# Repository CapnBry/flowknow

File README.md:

flowknow
========

ATmega-based flow meter and tally

Project directory structure
```
arduino/ - FlowKnow source code
eagle/   - Schematic and board design
```

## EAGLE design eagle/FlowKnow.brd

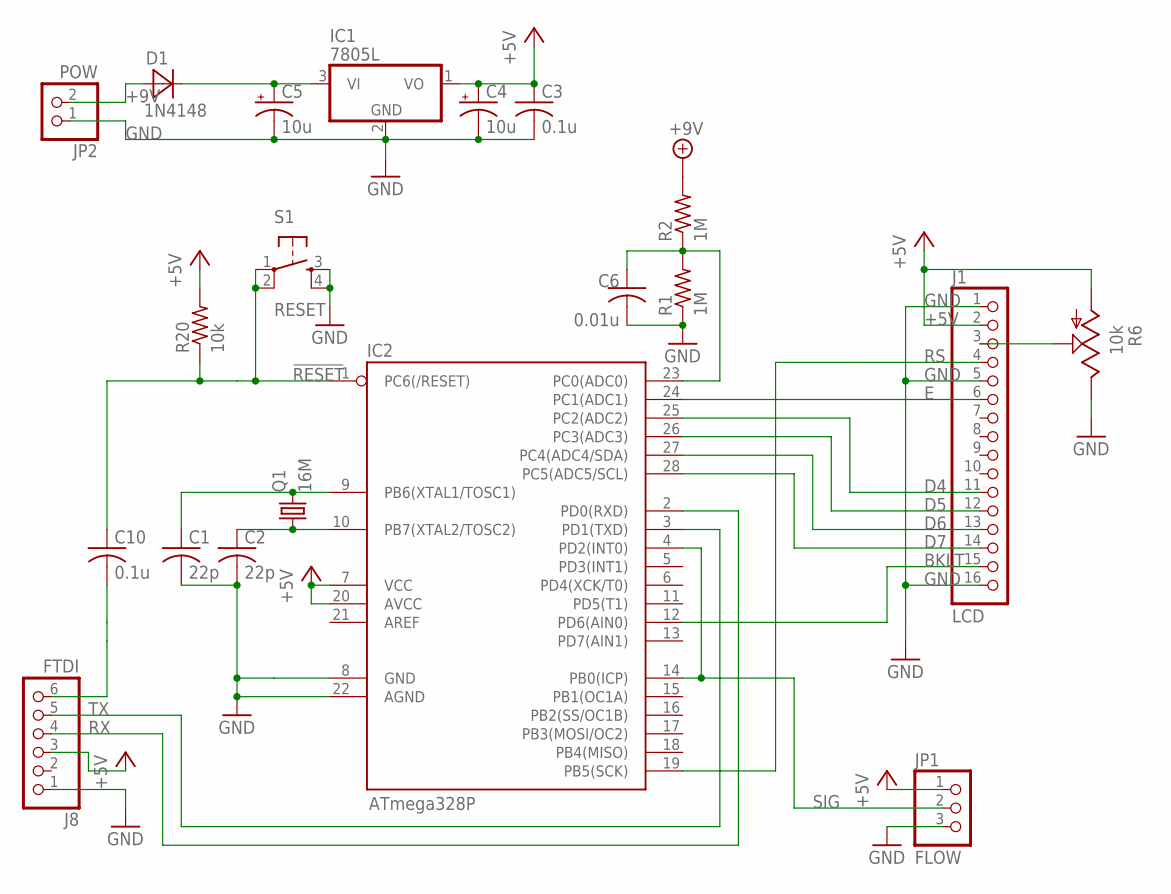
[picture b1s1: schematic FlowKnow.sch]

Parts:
C1, C2: 22p; C025-025X050
C3, C10: 0.1u; C025-025X050
C4: 10u; E2-4
C5: 10u; E2,5-5
C6: 0.01u; C025-025X050
D1: 1N4148; DO35-5
IC1: 7805L; TO92
IC2: ATmega328P; DIL28-3
J1: LCD; 1X16
J8: FTDI; 1X06/90
JP1: FLOW; 1X03/90
JP2: POW; 1X02
Q1: 16M; HC49/S
R1, R2: 1M; 0204/7
R6: 10k; CT6
R20: 10k; 0204/7
S1: RESET; TACTILE-PTH

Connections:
!RESET: C10.1, IC2.1 (PC6(/RESET)), R20.1, S1.1, S1.2
+5V: C3.1, C4.+, IC1.1 (VO), IC2.7 (VCC), IC2.20 (AVCC), J1.2, J8.3, JP1.1, R6.A, R20.2
+9V: D1.A, JP2.2, R2.2
BKLT: IC2.12 (PD6(AIN0)), J1.15
D4: IC2.25 (PC2(ADC2)), J1.11
D5: IC2.26 (PC3(ADC3)), J1.12
D6: IC2.27 (PC4(ADC4/SDA)), J1.13
D7: IC2.28 (PC5(ADC5/SCL)), J1.14
E: IC2.24 (PC1(ADC1)), J1.6
GND: C1.2, C2.2, C3.2, C4.-, C5.-, C6.2, IC1.2 (GND), IC2.8 (GND), IC2.22 (AGND), J1.1, J1.5, J1.16, J8.1, JP1.3, JP2.1, R1.1, R6.E, S1.3, S1.4
unnamed: C2.1, IC2.10 (PB7(XTAL2/TOSC2)), Q1.1
unnamed: C10.2, J8.6
unnamed: C1.1, IC2.9 (PB6(XTAL1/TOSC1)), Q1.2
unnamed: J1.3, R6.S
unnamed: C5.+, D1.C, IC1.3 (VI)
unnamed: C6.1, IC2.23 (PC0(ADC0)), R1.2, R2.1
RS: IC2.19 (PB5(SCK)), J1.4
RX: IC2.2 (PD0(RXD)), J8.4
SIG: IC2.4 (PD2(INT0)), IC2.14 (PB0(ICP)), JP1.2
TX: IC2.3 (PD1(TXD)), J8.5

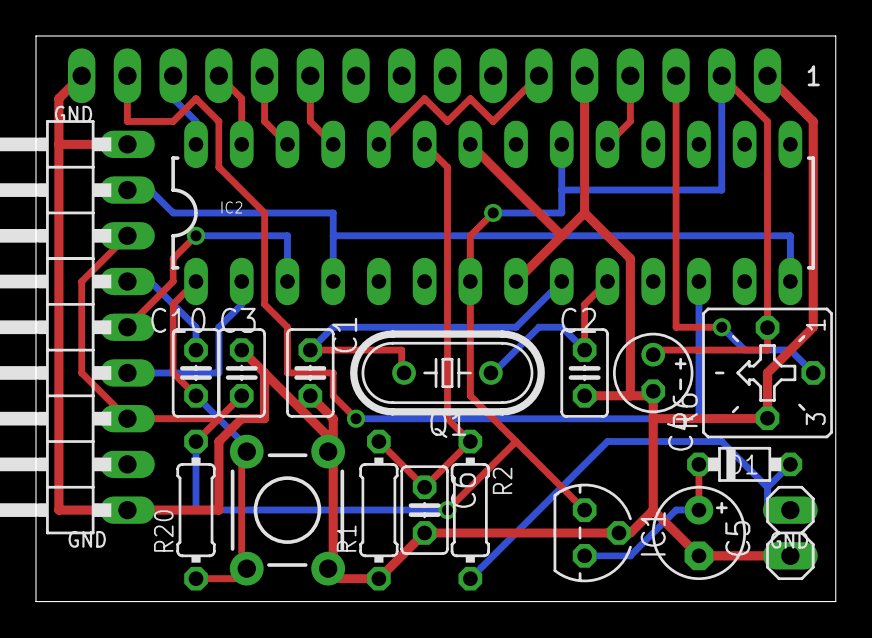
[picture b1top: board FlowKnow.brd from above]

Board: 2 copper layers, 44.4 x 31.4 mm, 20 parts (1 on the bottom side), 20 nets.

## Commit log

2013-04-02 [avr] Intial import
2013-04-02 README update
2013-10-21 [pcb] Unrouted PCB import
2014-01-24 [avr] Update to VS2012, line endings to CRLF
2014-01-24 [avr] Decouple the sensor reading from the LCD update to get more stable readings
    Old: Sensor read/LCD update 500ms, Animation 250ms
    New: Sensor read 1000ms, LCD update 666ms, Animation 333ms
    At 1 LPM that is only 2.5 ticks per the old 500ms update, it would either
    be 2 or 3 which is a 50% difference. Now it will get 4 5 or 6, which is
    only a 20% difference. The LCD will smooth between the updates
2014-01-24 [avr] Sleep with BOD enabled now
    There's no point in disabling the BOD when sleeping because the timers need
    to run so there's no going below IDLE.
2014-01-27 [avr] Fix overflow in timer count causing super-high lpm
    sleep() now always sleeps in exact multiples of LOOP_PERIOD
    Also move animation undate into the only place g_Liters changes, and time
    count to only where it changes
2014-01-27 [avr] Reduce LCD to 600ms and 2/2.5 smoothing from (66ms 2/3.0)
2014-01-27 [avr] Comment reminder what tone is for
2014-01-27 [avr] Update the sensor on the first loop
2014-01-27 [avr] Avoid potential buffer overflow in FloatPrint
2014-01-28 [avr] Variable sensor loop timing and coarse/fine smoothing. Requires 8MHz!
    -- Must be compiled with F_CPU 8Mhz now because sensor period can go over
    1s and will overflow TIMER1 counter. Will scale 16MHz CPU to 8MHz or
    DIV8 fused CPUs up to 8MHz.
    -- Sensor loop now scales between LOOPCNT_SENSOR_LO and LOOPCNT_SENSOR_HI
    depending on trigger count. Tries to prevent large variance caused by
    low frequency bouncing back and forth between e.g. 4-5Hz by extending
2014-01-28 [avr] Organization cleanup
2014-01-29 [avr] Add 0.5 LPM calibration
2015-02-24 [avr] Constrain FloatPrint prints to width so it doesn't spill over.
2015-02-24 [avr] Enter SLEEP_MODE_PWR_DOWN after 30 minutes of zero readings
2015-02-24 [avr] Update to Arduino 1.6.0
2015-08-12 [pcb] Update to use contrast pot instead of software (untested)
2015-08-12 [avr] Fix powerdown taking LOOPCNT_LCD times too long
